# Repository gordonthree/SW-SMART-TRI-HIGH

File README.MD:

# Triple High Side Smart Switch Node

Compact power management board intended to control three high-side DC loads. The node provides current monitoring of each load. Temperature and supply voltage are also monitored. This node works with other CAN-CTL modules using the robust CAN bus interface.

<IMG src="https://github.com/gordonthree/SW-SMART-TRI-HIGH/blob/main/SW-SMART-TRI-HIGH.png?raw=true" width=480>

* STM32G0B1KBTx 32-pin microcontroller
* Three BTS7002 Profet Smart Switches for high side loads, firmware limited to 15 amps each
* Microchip MCP2562 isolated CAN bus transceiver
* Automotive grade 5v switchmode power supply and linear 3.3v regulator
* Voltage divider to monitor supply voltage
* Switch current monitoring and diagnostics
* Three position screw terminal block for CAN bus connection
* Five position screw terminal block for power-out
* Heavy duty terminal block connectors for power in
* Headers for SWD programming and USART1 debug serial port

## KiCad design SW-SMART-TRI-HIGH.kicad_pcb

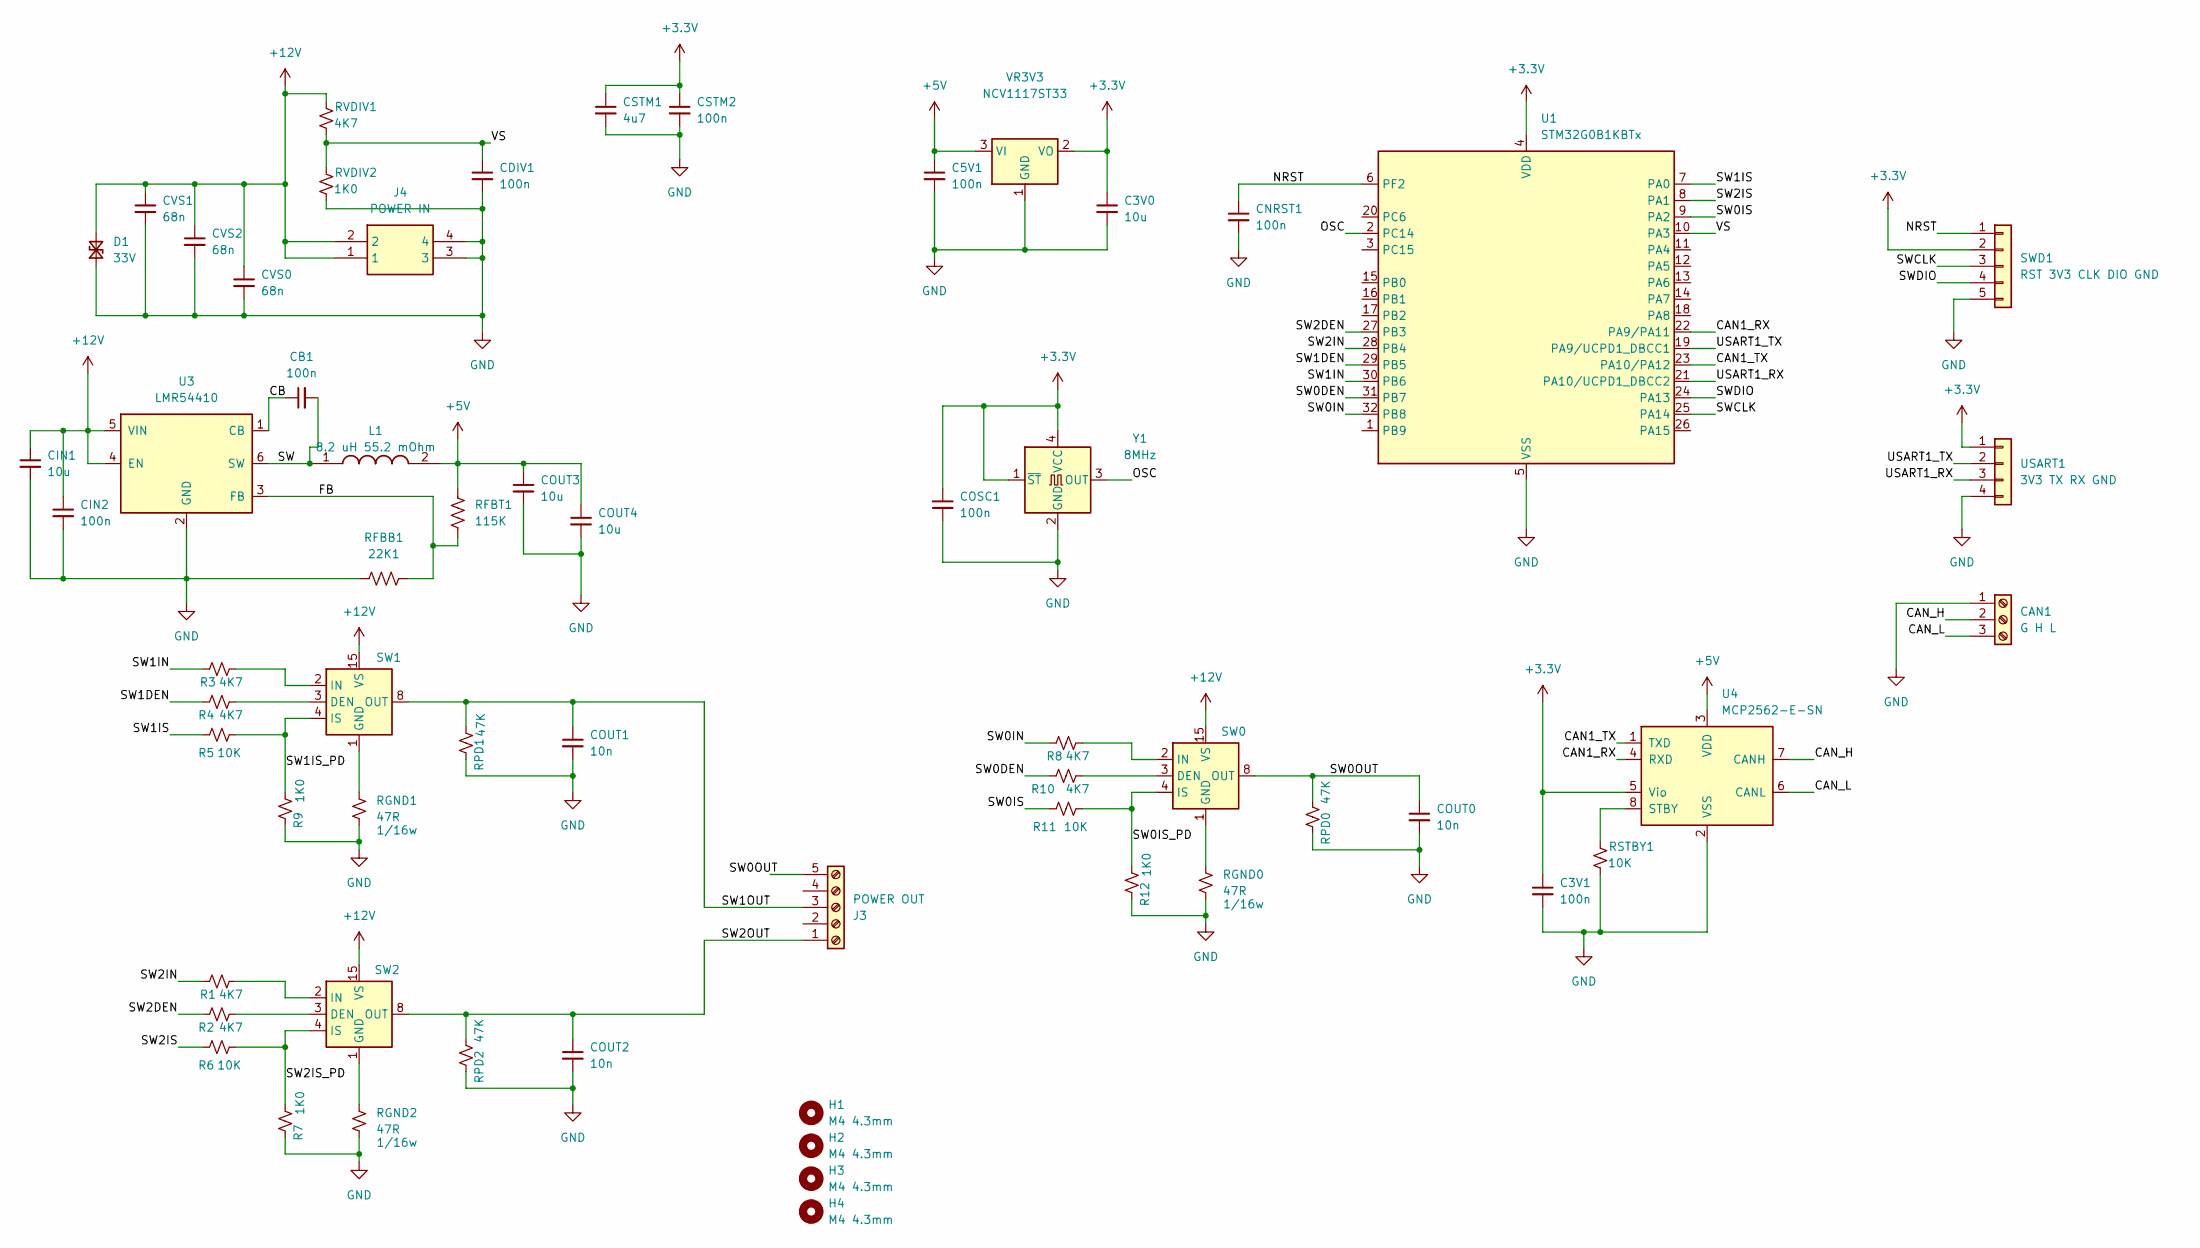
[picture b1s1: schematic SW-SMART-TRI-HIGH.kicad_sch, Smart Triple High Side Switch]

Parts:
C3V0: 10u; C_0805_2012Metric_Pad1.18x1.45mm_HandSolder
C3V1, C5V1: 100n; C_0603_1608Metric_Pad1.08x0.95mm_HandSolder
CAN1: G H L; TerminalBlock_Phoenix_MPT-0,5-3-2.54_1x03_P2.54mm_Horizontal
CB1: 100n; C_0603_1608Metric_Pad1.08x0.95mm_HandSolder
CDIV1: 100n; C_0603_1608Metric_Pad1.08x0.95mm_HandSolder
CIN1: 10u; C_1210_3225Metric_Pad1.33x2.70mm_HandSolder
CIN2: 100n; C_0603_1608Metric_Pad1.08x0.95mm_HandSolder
CNRST1: 100n; C_0603_1608Metric_Pad1.08x0.95mm_HandSolder
COSC1: 100n; C_0603_1608Metric_Pad1.08x0.95mm_HandSolder
COUT0, COUT1, COUT2: 10n; C_0603_1608Metric_Pad1.08x0.95mm_HandSolder
COUT3, COUT4: 10u; C_0805_2012Metric_Pad1.18x1.45mm_HandSolder
CSTM1: 4u7; C_0805_2012Metric_Pad1.18x1.45mm_HandSolder
CSTM2: 100n; C_0603_1608Metric_Pad1.08x0.95mm_HandSolder
CVS0, CVS1, CVS2: 68n; C_0603_1608Metric_Pad1.08x0.95mm_HandSolder
D1: 33V; D_SMA_Handsoldering
H1, H2, H3, H4: M4 4.3mm; MountingHole_4.3mm_M4
J3: POWER OUT; TerminalBlock_Phoenix_MKDS-3-5-5.08_1x05_P5.08mm_Horizontal
J4: POWER IN; VP0265840000G; Mouser Part Number 649-VP02658400J0G
L1: 8.2 uH 55.2 mOhm; SRP5030HMT2R2M; Mouser Part Number SRP5030HMT-8R2M
R1, R2, R3, R4, R8, R10: 4K7; R_0603_1608Metric_Pad0.98x0.95mm_HandSolder
R5, R6, R11: 10K; R_0603_1608Metric_Pad0.98x0.95mm_HandSolder
R7, R9, R12: 1K0; R_0603_1608Metric_Pad0.98x0.95mm_HandSolder
RFBB1: 22K1; R_0603_1608Metric_Pad0.98x0.95mm_HandSolder
RFBT1: 115K; R_0603_1608Metric_Pad0.98x0.95mm_HandSolder
RGND0, RGND1, RGND2: 47R; R_0603_1608Metric_Pad0.98x0.95mm_HandSolder
RPD0, RPD1, RPD2: 47K; R_0603_1608Metric_Pad0.98x0.95mm_HandSolder
RSTBY1: 10K; R_0603_1608Metric_Pad0.98x0.95mm_HandSolder
RVDIV1: 4K7; R_0603_1608Metric_Pad0.98x0.95mm_HandSolder
RVDIV2: 1K0; R_0603_1608Metric_Pad0.98x0.95mm_HandSolder
SW0, SW1, SW2: BTS7002-1EPP; SOP65P600X115-15N
SWD1: RST 3V3 CLK DIO GND; PinHeader_1x05_P2.54mm_Vertical
U1: STM32G0B1KBTx; LQFP-32_7x7mm_P0.8mm
U3: LMR54410; SOT-23-6
U4: MCP2562-E-SN; SOIC-8_3.9x4.9mm_P1.27mm
USART1: 3V3 TX RX GND; PinHeader_1x04_P2.54mm_Vertical
VR3V3: NCV1117ST33; SOT-223-3_TabPin2
Y1: 8MHz; Oscillator_SMD_XO-4Pin_3.2x2.5mm_HandSoldering

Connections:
+3.3V: C3V0.1, C3V1.1, COSC1.1, CSTM1.1, CSTM2.1, SWD1.2, U1.4 (VDD), U4.5 (Vio), USART1.1, VR3V3.2 (VO), Y1.1 (~ST), Y1.4 (VCC)
+5V: C5V1.1, COUT3.1, COUT4.1, L1.2, RFBT1.1, U4.3 (VDD), VR3V3.3 (VI)
+12V: CIN1.1, CIN2.1, CVS0.1, CVS1.1, CVS2.1, D1.2 (A2), J4.1, J4.2, RVDIV1.2, SW0.15 (VS), SW1.15 (VS), SW2.15 (VS), U3.4 (EN), U3.5 (VIN)
/CAN1_RX: U1.22 (PA9/PA11), U4.4 (RXD)
/CAN1_TX: U1.23 (PA10/PA12), U4.1 (TXD)
/CAN_H: CAN1.2, U4.7 (CANH)
/CAN_L: CAN1.3, U4.6 (CANL)
/CB: CB1.1, U3.1 (CB)
/FB: RFBB1.2, RFBT1.2, U3.3 (FB)
/NRST: CNRST1.1, SWD1.1, U1.6 (PF2)
/OSC: U1.2 (PC14), Y1.3 (OUT)
/SW: CB1.2, L1.1, U3.6 (SW)
/SW0DEN: R10.1, U1.31 (PB7)
/SW0IN: R8.1, U1.32 (PB8)
/SW0IS: R11.1, U1.9 (PA2)
/SW0IS_PD: R11.2, R12.2, SW0.4 (IS)
/SW0OUT: COUT0.1, J3.5, RPD0.2, SW0.8 (OUT), SW0.9 (OUT), SW0.10 (OUT), SW0.12 (OUT), SW0.13 (OUT), SW0.14 (OUT)
/SW1DEN: R4.1, U1.29 (PB5)
/SW1IN: R3.1, U1.30 (PB6)
/SW1IS: R5.1, U1.7 (PA0)
/SW1IS_PD: R5.2, R9.2, SW1.4 (IS)
/SW1OUT: COUT1.1, J3.3, RPD1.2, SW1.8 (OUT), SW1.9 (OUT), SW1.10 (OUT), SW1.12 (OUT), SW1.13 (OUT), SW1.14 (OUT)
/SW2DEN: R2.1, U1.27 (PB3)
/SW2IN: R1.1, U1.28 (PB4)
/SW2IS: R6.1, U1.8 (PA1)
/SW2IS_PD: R6.2, R7.2, SW2.4 (IS)
/SW2OUT: COUT2.1, J3.1, RPD2.2, SW2.8 (OUT), SW2.9 (OUT), SW2.10 (OUT), SW2.12 (OUT), SW2.13 (OUT), SW2.14 (OUT)
/SWCLK: SWD1.3, U1.25 (PA14)
/SWDIO: SWD1.4, U1.24 (PA13)
/USART1_RX: U1.21 (PA10/UCPD1_DBCC2), USART1.3
/USART1_TX: U1.19 (PA9/UCPD1_DBCC1), USART1.2
/VS: CDIV1.1, RVDIV1.1, RVDIV2.2, U1.10 (PA3)
GND: C3V0.2, C3V1.2, C5V1.2, CAN1.1, CDIV1.2, CIN1.2, CIN2.2, CNRST1.2, COSC1.2, COUT0.2, COUT1.2, COUT2.2, COUT3.2, COUT4.2, CSTM1.2, CSTM2.2, CVS0.2, CVS1.2, CVS2.2, D1.1 (A1), J4.3, J4.4, R7.1, R9.1, R12.1, RFBB1.1, RGND0.2, RGND1.2, RGND2.2, RPD0.1, RPD1.1, RPD2.1, RSTBY1.1, RVDIV2.1, SWD1.5, U1.5 (VSS), U3.2 (GND), U4.2 (VSS), USART1.4, VR3V3.1 (GND), Y1.2 (GND)
unnamed: R10.2, SW0.3 (DEN)
unnamed: RGND0.1, SW0.1 (GND)
unnamed: R8.2, SW0.2 (IN)
unnamed: R4.2, SW1.3 (DEN)
unnamed: RGND1.1, SW1.1 (GND)
unnamed: R3.2, SW1.2 (IN)
unnamed: R2.2, SW2.3 (DEN)
unnamed: RGND2.1, SW2.1 (GND)
unnamed: R1.2, SW2.2 (IN)
unnamed: RSTBY1.2, U4.8 (STBY)

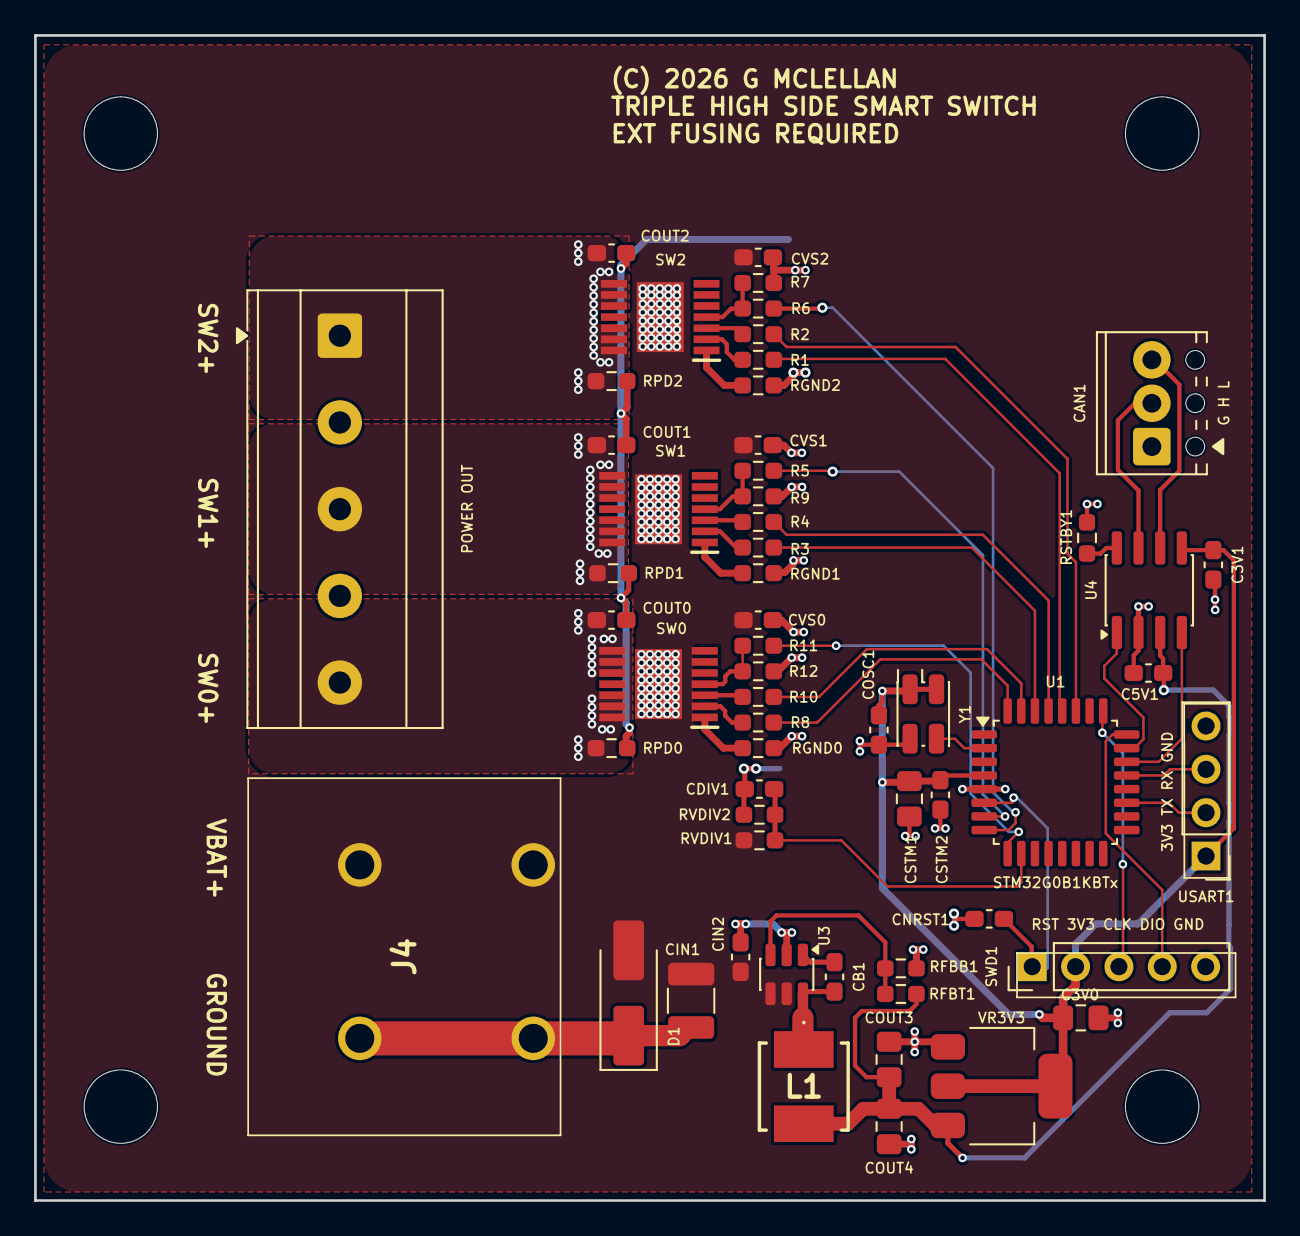
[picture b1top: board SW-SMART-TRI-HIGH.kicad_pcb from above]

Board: 2 copper layers, 72.0 x 68.2 mm, 61 parts (0 on the bottom side), 43 nets.

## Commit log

2026-01-19 update the readme
2026-01-20 added 3d rendering
2026-01-20 schematic and layout mostly complete
2026-01-20 update embedded image
2026-01-20 update details
2026-01-20 updated rendering
2026-01-20 fattened up some tracks
2026-01-20 renamed power in connector
2026-01-26 switch to smps for 5v, adjust CAN and SWD pin connections
2026-01-26 improve ground connections, cleanup silkscreen
2026-01-30 fixed some footprints, made the +12v pour a bit bigger on the bottom side
2026-01-30 updated rendering to include 5v SMPS
2026-01-30 update readme format
2026-02-02 add 8mhz XO, fix some footprint issues
2026-02-02 updated rendering after adding XO

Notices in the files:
SW-SMART-TRI-HIGH.kicad_pcb:
(C) 2026 G MCLELLAN
